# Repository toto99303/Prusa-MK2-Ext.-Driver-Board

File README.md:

# Prusa-MK2-Ext.-Driver-Board
So, what is this? This is an external stepper driver board for X and Y stepper motors of the original Prusa MK2/MK2S/MK2.5/MK2.5S printers. It allows usage of TMC2100/TMC2208/TMC2209 drivers (Silent Step Stick and similar, (TMC2209 are recommended), so your printer will become a lot quieter and much smoother due to the 256 step interpolation (same as on the MK3). This is the latest upgraded version 2.4.1 of the board.  

More info here:  
https://vmod.wordpress.com/prusa-mk2s-ext-driver-board-v2-3/

BOM:

1 x wire-to-board header 3 POS 2.54MM(.100) (https://www.digikey.be/en/products/detail/cvilux-usa/CI3103P1V00-NH/13177511)

2 x 100uF 35V Capacitors (https://www.digikey.be/en/products/detail/rubycon/35ZLH100MEFC6-3X11/3134256)

2 x 10k through hole resistors (https://www.digikey.be/en/products/detail/stackpole-electronics-inc/RNF14BTE10K0/1682687)

1 x 2 way terminal block (https://www.tme.eu/en/details/dg306-5.0-2p12/pcb-terminal-blocks/degson-electronics/dg306-5-0-02p-12-00a-h/)

1 x right angle 2.54mm pin header 2x4 pins (https://jlcpcb.com/partdetail/Cvilux-CH81802H200/C918394)

2 x right angle dupont 1x4 MX2.54 TJC8 housing (https://vi.aliexpress.com/item/1005004362274135.html?gatewayAdapt=glo2vnm)

4 x driver header 1x8 2.54mm (https://grobotronics.com/pin-header-1x8-female-2.54mm.html?sl=en)

1 x IDC connector 2x4 wire-to-board connector (https://www.digikey.com/en/products/detail/cvilux-usa/CA2308PA10Z/15519128)

10-15cm short flat ribbon cable (https://www.digikey.com/en/products/detail/assmann-wsw-components/AWG28-16-G-300/655756)

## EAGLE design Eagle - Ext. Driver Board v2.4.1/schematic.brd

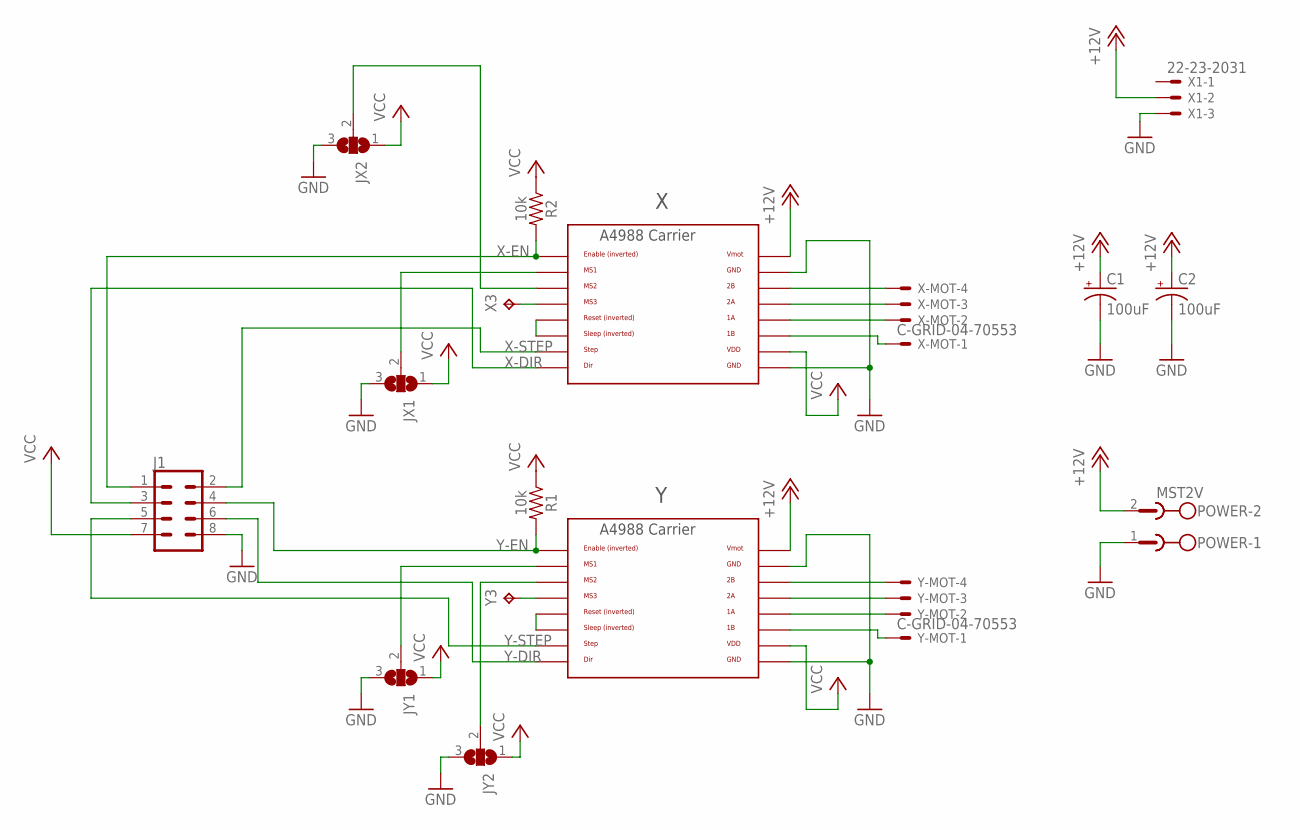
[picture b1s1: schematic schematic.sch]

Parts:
C1, C2: 100uF; CPOL-RADIAL-2.5MM-6.5MM
J1: CONN_04X2; 2X4
JX1, JX2: SJ2W; SJ_2
JY1, JY2: SJ2W; SJ_2
POWER: MST2V; MSTBV2
R1, R2: 10k; AXIAL-0.3
U$1, U$4: A4988BREAKOUT
X1: 22-23-2031
X3: TPB1,27; B1,27
X-MOT: C-GRID-04-70553; 70553-04
Y3: TPB1,27; B1,27
Y-MOT: C-GRID-04-70553; 70553-04

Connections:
+12V: C1.1 (+), C2.1 (+), POWER.2, U$1.VMOT, U$4.VMOT, X1.2
GND: C1.2 (-), C2.2 (-), J1.8, JX1.3, JX2.3, JY1.3, JY2.3, POWER.1, U$1.GND, U$1.GND@0 (GND), U$4.GND, U$4.GND@0 (GND), X1.3
unnamed: JY2.2, U$4.MS2
unnamed: U$4.MS3, Y3.TP
unnamed: U$4.2B, Y-MOT.4
unnamed: U$4.2A, Y-MOT.3
unnamed: U$1.RST, U$1.SLP (SLEEP)
unnamed: U$1.2B, X-MOT.4
unnamed: U$1.2A, X-MOT.3
unnamed: U$4.RST, U$4.SLP (SLEEP)
unnamed: U$1.1A, X-MOT.2
unnamed: U$4.1A, Y-MOT.2
unnamed: U$4.1B, Y-MOT.1
unnamed: U$1.1B, X-MOT.1
unnamed: JX2.2, U$1.MS2
unnamed: U$1.MS3, X3.TP
unnamed: JX1.2, U$1.MS1
unnamed: JY1.2, U$4.MS1
VCC: J1.7, JX1.1, JX2.1, JY1.1, JY2.1, R1.P$1 (1), R2.P$1 (1), U$1.VDD, U$4.VDD
X-DIR: J1.3, U$1.DIR
X-EN: J1.1, R2.P$2 (2), U$1.EN
X-STEP: J1.2, U$1.STEP
Y-DIR: J1.6, U$4.DIR
Y-EN: J1.4, R1.P$2 (2), U$4.EN
Y-STEP: J1.5, U$4.STEP

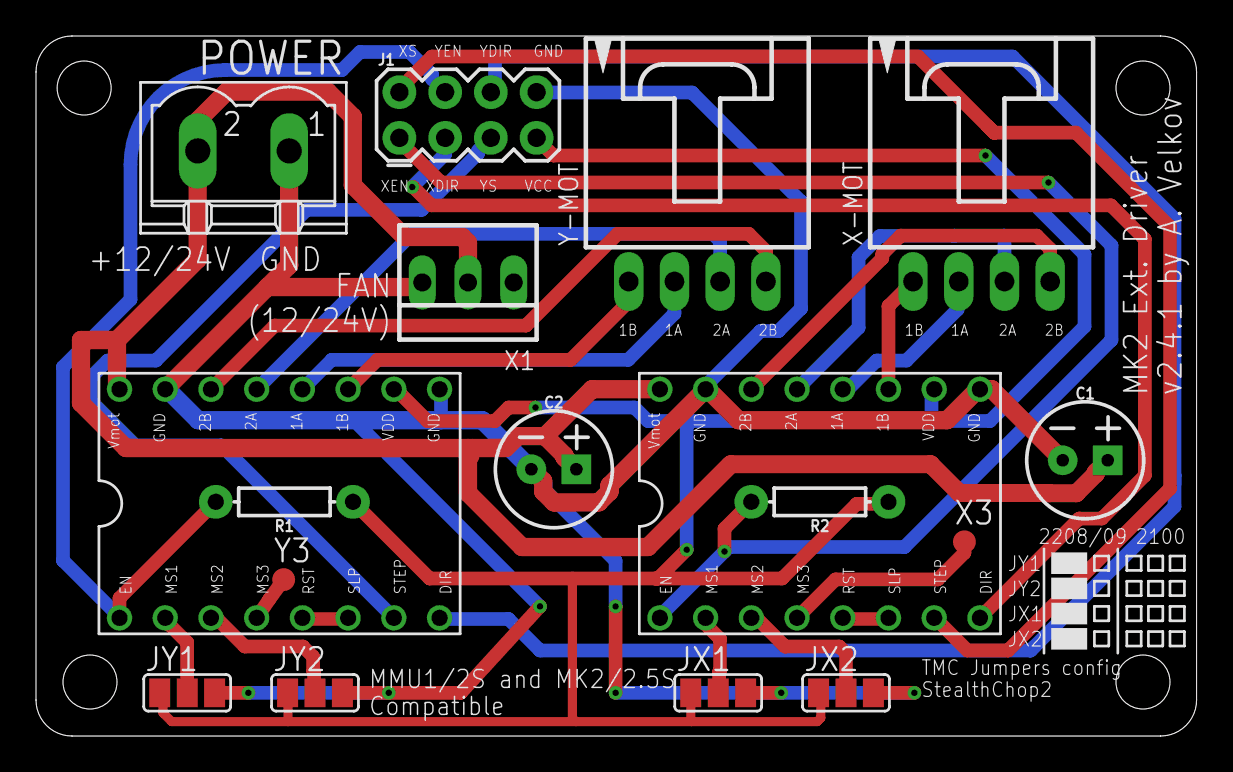
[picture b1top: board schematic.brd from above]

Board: 2 copper layers, 64.5 x 38.9 mm, 17 parts (0 on the bottom side), 25 nets.

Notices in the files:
parts and their libraries:
SparkFun-Connectors: Licensing: Creative Commons ShareAlike 4.0 International - https://creativecommons.org/licenses/by-sa/4.0
